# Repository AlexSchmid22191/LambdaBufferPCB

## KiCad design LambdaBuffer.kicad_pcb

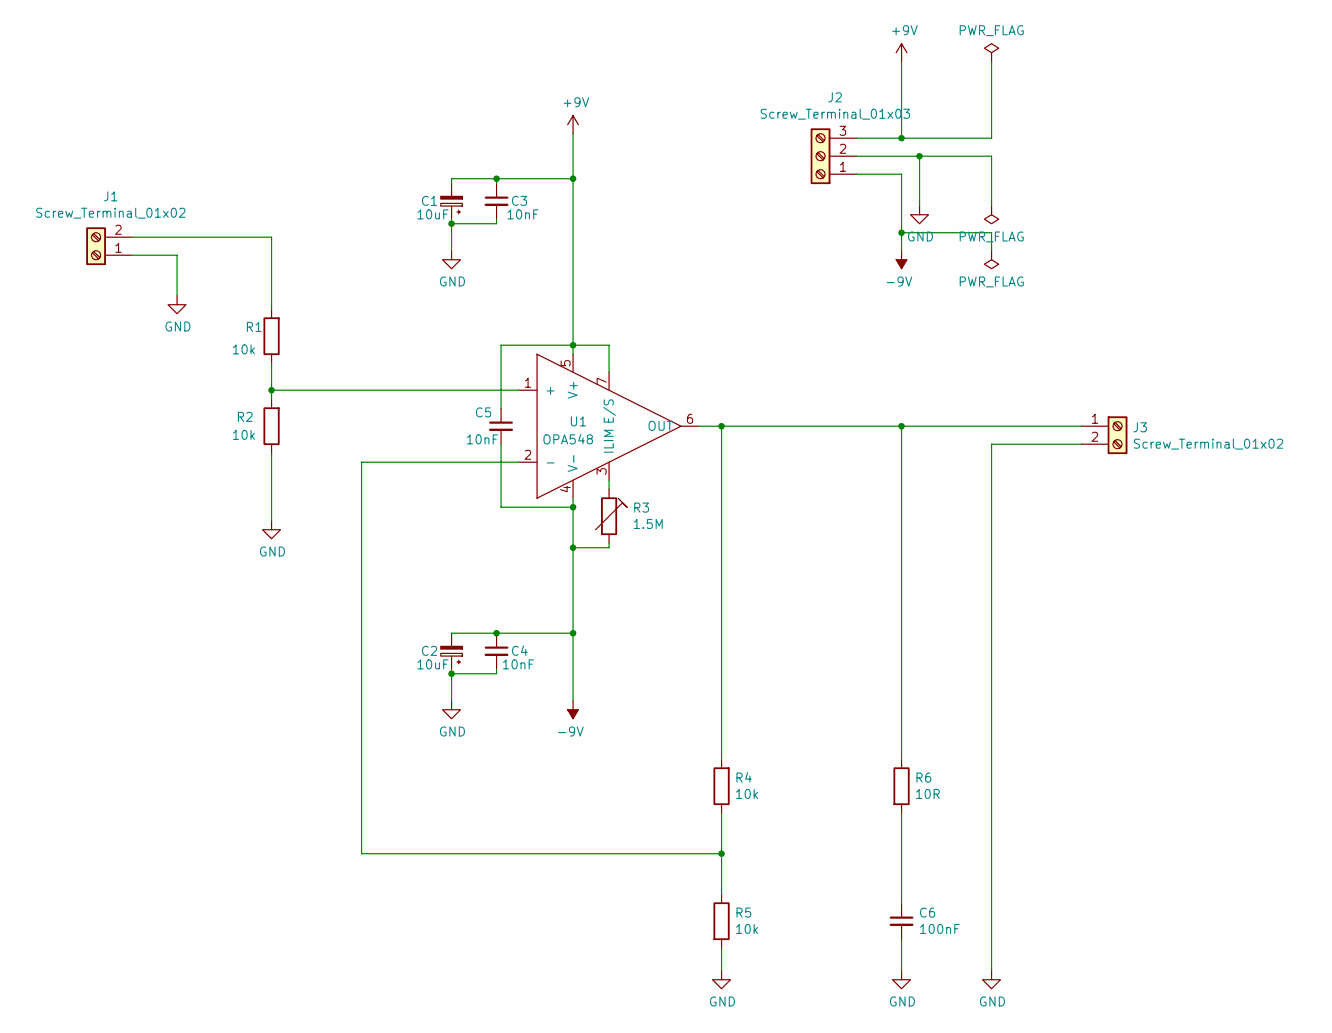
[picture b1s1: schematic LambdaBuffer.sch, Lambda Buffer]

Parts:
C1, C2: 10uF; C_0603_1608Metric_Pad1.05x0.95mm_HandSolder
C3, C4, C5: 10nF; C_0603_1608Metric_Pad1.05x0.95mm_HandSolder
C6: 100nF; C_0603_1608Metric_Pad1.05x0.95mm_HandSolder
J1, J3: Screw_Terminal_01x02; TerminalBlock_bornier-2_P5.08mm
J2: Screw_Terminal_01x03; TerminalBlock_bornier-3_P5.08mm
R1, R2, R4, R5: 10k; R_0603_1608Metric_Pad1.05x0.95mm_HandSolder
R3: 1.5M; Potentiometer_Bourns_3314J_Vertical
R6: 10R; R_0603_1608Metric_Pad1.05x0.95mm_HandSolder
U1: OPA548; TO-220-7

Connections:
+9V: C1.2, C3.1, C5.1, J2.3, U1.5 (V+), U1.7 (E/S)
-9V: C2.2, C4.1, C5.2, J2.1, R3.2, U1.4 (V-)
GND: C1.1, C2.1, C3.2, C4.2, C6.2, J1.1, J2.2, J3.2, R2.1, R5.2
unnamed: C6.1, R6.2
unnamed: J1.2, R1.2
unnamed: J3.1, R4.2, R6.1, U1.6 (OUT)
unnamed: R1.1, R2.2, U1.1 (+)
unnamed: R3.1, U1.3 (ILIM)
unnamed: R4.1, R5.1, U1.2 (-)

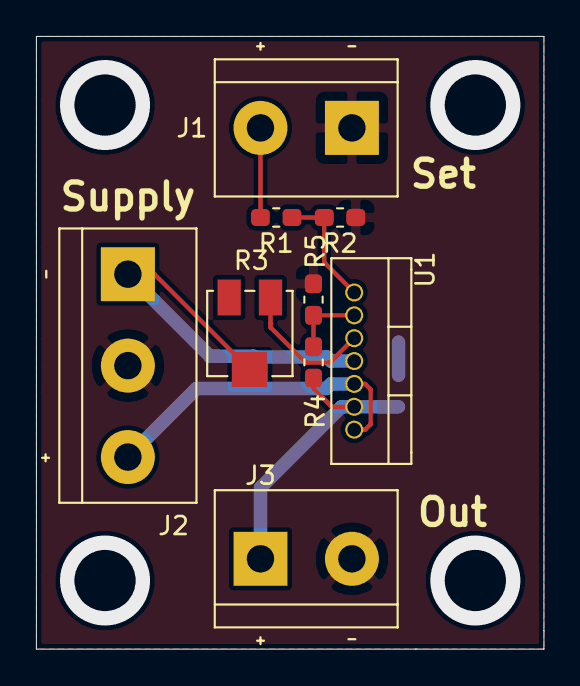
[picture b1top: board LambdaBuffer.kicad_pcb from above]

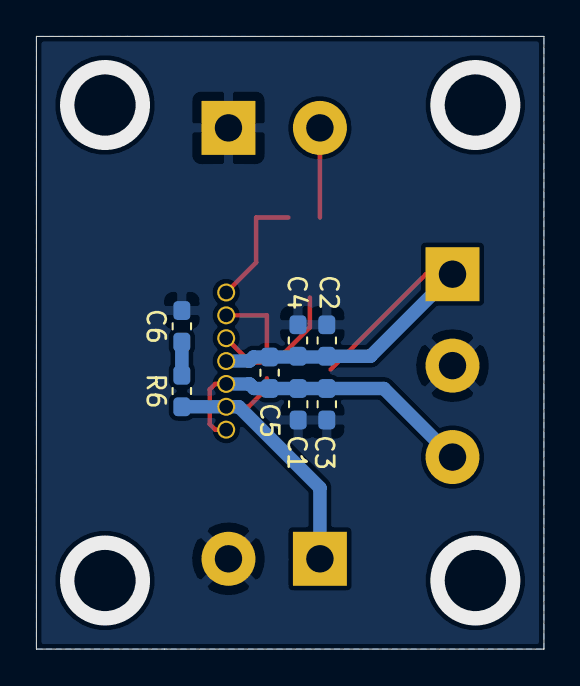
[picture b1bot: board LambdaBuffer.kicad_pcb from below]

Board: 2 copper layers, 28.2 x 34.0 mm, 16 parts (7 on the bottom side), 9 nets.

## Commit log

2021-03-04 Initial
